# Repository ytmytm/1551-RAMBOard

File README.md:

# 1551-RAMBOard (First Bank)

This project adds **8K of RAM** and **8K of extra ROM space** to a **Commodore 1551** disk drive by replacing the ROM with a small daughterboard. The extra memory is used by a ROM patch to implement a simple **track cache**: read an entire track once, then serve subsequent sector reads from RAM.

A 27x (relative to 1541) / 7x (relative to 1551) fastloader is provided.

The mod and patched ROM are detected and utilized by [Parobek ROM](https://github.com/ytmytm/plus4-parobek).

## What you get

- **RAM expansion**: `$8000-$9FFF` (8K) mapped to SRAM on the daughterboard.
- **Extra ROM window**: `$A000-$BFFF` (8K) mapped to the *upper* part of a larger ROM image.
- **Two DOS ROMs**: with a 64K ROM chip, you can add a switch to select either the stock 1551 ROM or the patched ROM
- **Two patched variants**: stock 1551 (318008-01) and [SuperDOS](https://plus4world.powweb.com/dl/utils/s/super_dos_1551.rom) (40-track disks)
- **HypaRAM**: fastloader
- **Parobek support**: even faster fastloader startup when drivecode is embedded in patched ROM

## Videos

<a href="https://www.youtube.com/watch?v=vWi2URbmIlo" target="_blank">
 <small>Click for 1551 demonstration, loading a 108 block file</small></p>
</a>

<a href="https://www.youtube.com/watch?v=xZMYda7cszA" target="_blank">
 <small>Click for Pi1551 HypaRAM demonstration, loading a 220 block file</small></p>
</a>

## Hardware

This board plugs into the original ROM socket and adds:

- **SRAM**: 8Kx8 (6264) or 32Kx8 (e.g. 62256). Only 8K is used by default; the remaining space is reserved for future banking options.
- **ROM**: 27C512/27E512 (64K). The board maps the active 32K half into `$8000-$FFFF`, but `$8000-$9FFF` is covered by RAM, so effectively the ROM is visible at `$A000-$FFFF` (24K). This is exactly the same setup as DolphinDOS on 1571
- **Glue logic**: `74LS139` + `74LS00`.

### BOM

- 1x 14-pin DIP socket
- 1x 16-pin DIP socket
- 2x 28-pin DIP socket
- 2x 14-pin round pinheaders ("precision" ones)
- 2x 10K resistors
- 1x 74LS00 (or HCT)
- 1x 74LS139 (or HCT)
- 1x 27E256 / 27E512 (32K or 64K EEPROM)
- 1x 6264 or 62256 (8K or 32K SRAM)
- 1x switch (for ROM selection: open or closed)

### Assembly

1. Start by soldering the pin headers to the holes marked "pins". Make sure their longer sections point toward the bottom. The board uses these to plug into the existing ROM socket.

2. Solder the remaining components: two resistors, then the sockets.

3. Flash the EEPROM with a ROM image from the Releases tab (or build your own with `make`). Use `1551.318008-01-64k.bin` for stock DOS or `super_dos_1551-64k.bin` for SuperDOS 40-track support. The 64K image contains the patched ROM in the top half (selected by default when `J1` is open), so you do not need to connect the switch yet.

4. Insert the chips into their sockets.

5. Open the 1551, remove the ROM chip (U4), and plug the board in its place. Ensure correct pin alignment.

6. Connect the remaining signals—`A14`, `A15`, and `R/~W`—as described in the Wiring section below.

### Wiring

- **J1 (ROM bank select for 27C512)**:
  - **short**: bottom 32K of the 64K ROM
  - **open**: top 32K of the 64K ROM
- **J2 (3-wire tap from the 1551 mainboard)**:
  - **A14** from CPU **U2 pin 21** (or **U7 pin 7**)
  - **A15** from CPU **U2 pin 22** (or **U7 pin 6**)
  - **R/~W**: **do not** take raw R/W directly from the CPU. Use the qualified R/~W that actually goes to RAM:
    - onboard RAM **U5 pin 21**, or
    - **U3 pin 19**

### Jumpers

`RAM_A13` and `RAM_A14` jumpers are configured in such a way that you can plug in either SRAM 6264 (8K) or 62256 (32K) with no other changes.
If a method to latch two bits for the necessary port selection is found, then with 62256 (32K) four banks of 8K could be selected - e.g. for a permanent cache of the directory track.

### Quickstart

1. Install the hardware and keep J1 open
2. Use a 27E512 ROM with a 64K image from Releases (`1551.318008-01-64k.bin` or `super_dos_1551-64k.bin`)
3. Try running a simple BASIC program to read the ROM at `$a000` - with J1 open it should be the top, patched half with `RAM` signature
4. If you see `RAM` in the output and you can load the directory then everything works - directory track was already put into cache

```
10 open 15,8,15,"m-r"+chr$(0)+chr$(160)+chr$(3)
20 for i=1 to 3
30 get#15,b$
40 print asc(b$);b$
50 next
60 close 15
```

## Project files (KiCad)

Everything you need is attached to the Release page too.

- [KiCad project](kicad/1551-RAMBoard-FirstBank/)
- [Schematic PDF](kicad/1551-RAMBoard-FirstBank/plots/1551-RAMBoard2-FirstBank.pdf)
- [Gerbers](kicad/1551-RAMBoard-FirstBank/plots/)

## Firmware patch / build

The patcher is a single KickAssembler source file: `rampatch.asm`. It can patch either the stock 1551 ROM or SuperDOS 1551; the Makefile selects the base ROM via KickAssembler `-define` flags (`ROM1551` or `SUPERDOS1551`).

SuperDOS is the only other common 1551 DOS alternative. It adds 40-track disk support (similar in spirit to C64 SpeedDOS/DolphinDOS). The RAMBOard hook sites do not overlap with SuperDOS changes, so the same track-cache patch applies cleanly. Patch4 (ROM checksum bypass) is omitted for the SuperDOS build because SuperDOS already NOPs that routine.

### Source ROMs

Place these in `rom/` (or let `make` download them):

| File | Description |
|------|-------------|
| `rom/1551.318008-01.bin` | Stock 1551 DOS ([zimmers.net](https://www.zimmers.net/anonftp/pub/cbm/firmware/drives/new/1551/1551.318008-01.bin)) |
| `rom/super_dos_1551.bin` | SuperDOS 1551, 40 tracks ([plus4world](https://plus4world.powweb.com/dl/utils/s/super_dos_1551.rom)) |

### Windows (build.bat)

**Requirements**

- Java
- [KickAssembler](http://www.theweb.dk/KickAssembler/Main.html#frontpage) at `tools/KickAss.jar`
- Stock 1551 ROM at `rom/1551.318008-01.bin`

**Build**

```bat
build.bat
```

This builds the stock-ROM variant only:

- `1551.318008-01-patched.bin` — patched 32K ROM image
- `1551.318008-01-64k.bin` — 64K EPROM image (stock ROM in the lower half, patched ROM in the upper half)

For the SuperDOS variant, use the Linux Makefile (or invoke KickAssembler manually with `-define SUPERDOS1551`).

### Linux (Makefile)

**Requirements**

- `make`
- Java
- [KickAssembler](http://www.theweb.dk/KickAssembler/Main.html#frontpage) at `tools/KickAss.jar`
- [ACME](https://sourceforge.net/projects/acme-crossass/) assembler (`acme`)
- `curl` or `wget` (optional; used to auto-download source ROMs)

**Build everything**

```sh
make
```

This produces all deliverables:

| Output | Description |
|--------|-------------|
| `1551.318008-01-patched.bin` | Patched 32K ROM (stock 1551 base) |
| `1551.318008-01-64k.bin` | 64K EPROM image (stock + patched) |
| `super_dos_1551-patched.bin` | Patched 32K ROM (SuperDOS 40-track base) |
| `super_dos_1551-64k.bin` | 64K EPROM image (SuperDOS + patched) |
| `hyparam_1551.prg` | HypaRAM fastloader wedge |

**Other targets**

```sh
make help          # list all targets
make superrom      # SuperDOS patched 32K + 64K images only
make clean         # remove all build outputs (keeps source ROMs in rom/)
make test          # VICE xplus4 with stock patched ROM + RAM expansion
make test-super    # VICE xplus4 with SuperDOS patched ROM + RAM expansion
```

Each 64K image is suitable for 27C512/27E512 EPROMs:

- First 16K: `$FF` bytes (EPROM neutral)
- Next 16K: unpatched base ROM (stock or SuperDOS)
- Upper 32K: patched ROM with track cache and fastloader

## HypaRAM fastloader wedge

An example fastloader wedge called **HypaRAM** is included in the `src/` directory as `hypainstall14f0.s`, which
generates `hyparam_1551.prg`.

When loaded it will intercept LOAD operations and will run the fastloader embedded in the patched drive ROM directly.
With track cache the speedup is approximately **27x** relative to 1541 and **7x** relative to stock 1551.

For simplicity it supports only device #8 and doesn't check if the ROM was patched.

The same fastloader is embedded in [Parobek ROM](https://github.com/ytmytm/plus4-parobek) and will be autodetected for LOAD operations.

### Building HypaRAM

To build the binary `hyparam_1551.prg`, you need the [ACME assembler](https://sourceforge.net/projects/acme-crossass/).

- **Windows**:  
  ```
  acme hypainstall14f0.s
  ```

- **Linux/Unix/WSL**:  
  ```
  make
  ```

The produced binary `hyparam_1551.prg` can be loaded into C16/+4 emulators or real hardware with the RAMBoard installed.

## Testing in VICE

This repo contains `docs/vice-1551-ram-expansion.patch`, which documents the changes needed for VICE to emulate:

- 1551 RAM expansion at `$8000-$9FFF`
- the 32K ROM mapping with RAM overlay

## ROM signature / API stub

The patched ROM contains a small fixed-location signature and a public jump table:

- `$A000-$A002`: ASCII signature `"RAM"` (used to detect that the patched ROM is active)
- `$A003...`: jump table entries

This is used by the HypaRAM fastloader and [Parobek ROM](https://github.com/ytmytm/plus4-parobek).

## Theory of operation

### Address space

The onboard logic enables ROM only in `$C000-$FFFF` range. We ignore this signal and instead use CPU's A15 line as a trigger which signals that `$8000-$FFFF` range is being accessed.

The 74LS139 logic uses A14 to further divide that range to generate chip select signals for RAM in `$8000-$9FFF` range and for ROM in `$A000-$FFFF`.

### Track cache logic

When the drive firmware requests a sector read:

- If the requested track is already cached, the sector is copied from expanded RAM into the target buffer and execution returns to the original ROM flow.
- Otherwise, the patched code reads the entire track, caching **decoded sector data** in expanded RAM and collecting sector numbers from headers to build the lookup table.

The whole track is captured within **one disk revolution** (about **200 ms at 300 rpm**).

### GCR decoding on 1551

Unlike 1541-class drives, the 1551 ROM already decodes GCR **on the fly** during reads (made possible by the 2 MHz CPU). The patch reuses the same approach.

## Related

- design for 1541: [**1541-RAMBOard**](https://github.com/ytmytm/1541-RAMBOardII)
- design for 1571: [**1571 Track Cache ROM**](https://github.com/ytmytm/1571-TrackCacheROM)

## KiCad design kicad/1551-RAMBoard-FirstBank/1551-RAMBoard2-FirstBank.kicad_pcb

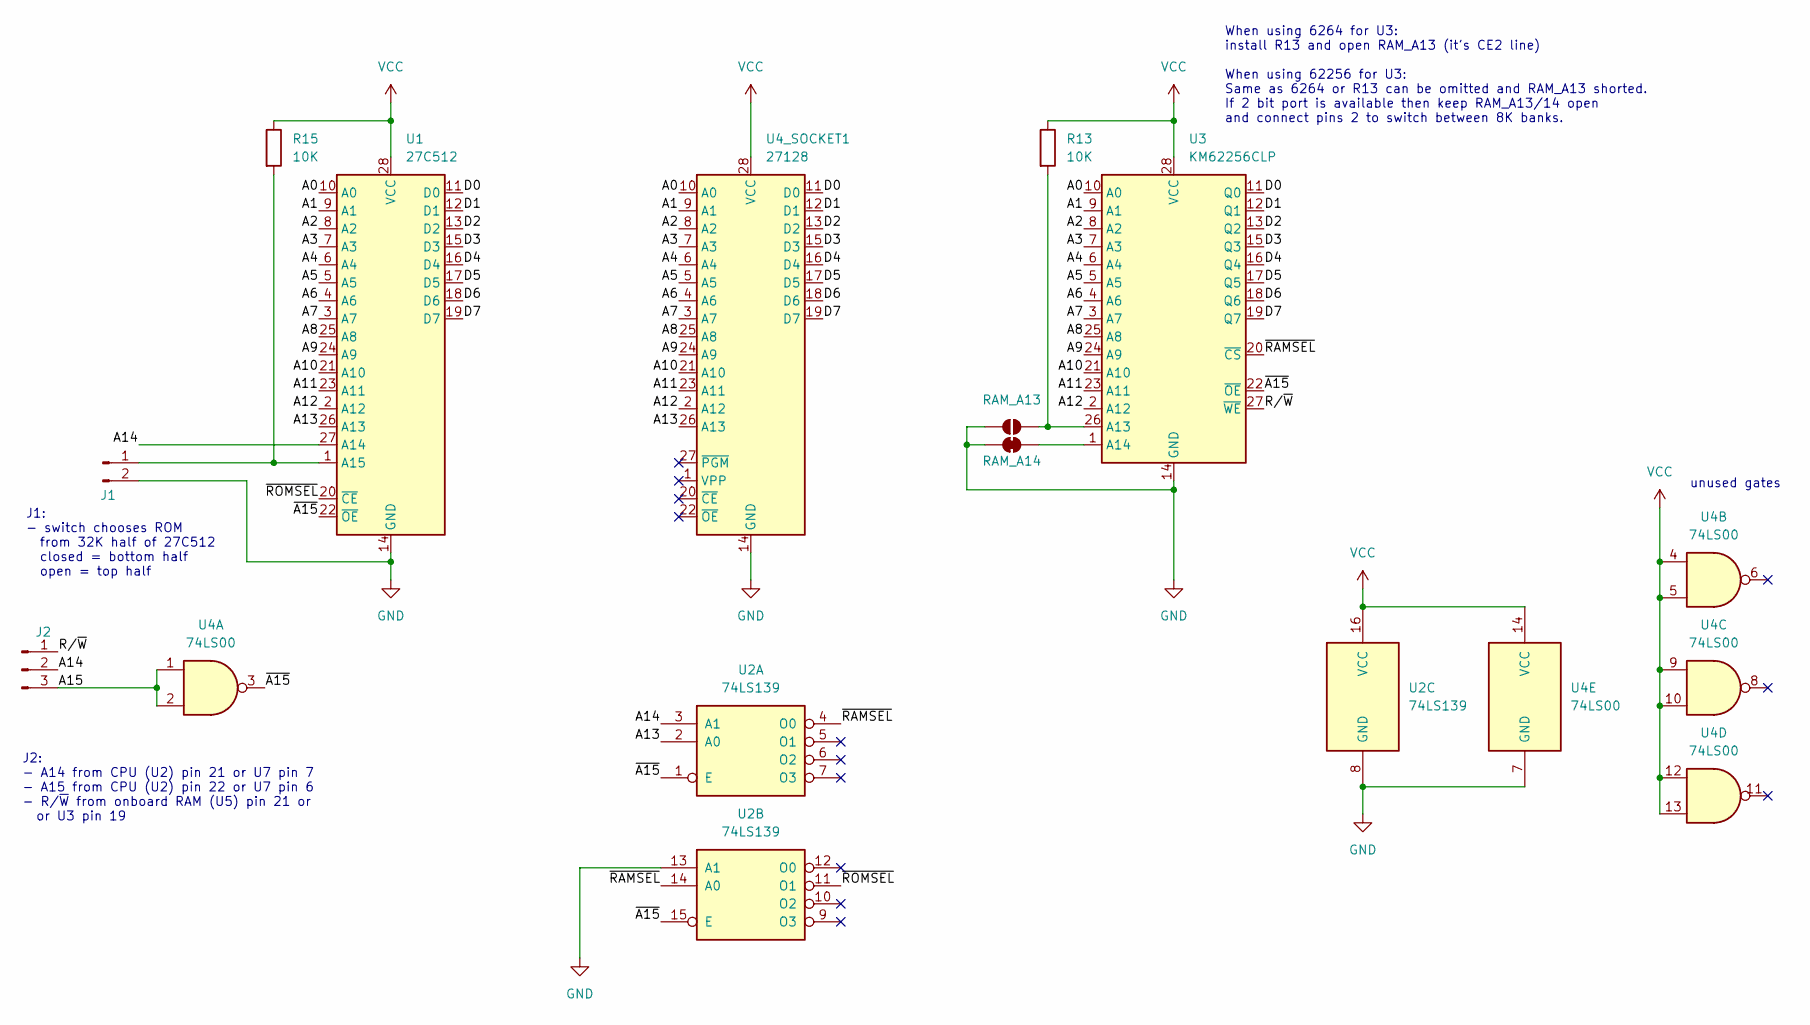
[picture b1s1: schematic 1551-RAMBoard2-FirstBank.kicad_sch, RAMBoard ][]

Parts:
J1: Conn_01x02_Pin; PinHeader_1x02_P2.54mm_Vertical
J2: Conn_01x03_Pin; PinHeader_1x03_P2.54mm_Vertical
R13, R15: 10K; R_Axial_DIN0207_L6.3mm_D2.5mm_P7.62mm_Horizontal
RAM_A13: SolderJumper_2_Open; SolderJumper-2_P1.3mm_Open_RoundedPad1.0x1.5mm
RAM_A14: SolderJumper_2_Bridged; SolderJumper-2_P1.3mm_Bridged_RoundedPad1.0x1.5mm
U1: 27C512; DIP-28_W15.24mm_Socket_LongPads
U2: 74LS139; DIP-16_W7.62mm_Socket_LongPads
U3: KM62256CLP; DIP-28_W15.24mm_Socket_LongPads
U4: 74LS00; DIP-14_W7.62mm_Socket_LongPads
U4_SOCKET1: 27128; DIP-28_W15.24mm_Socket_LongPads

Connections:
/A0: U1.10 (A0), U3.10 (A0), U4_SOCKET1.10 (A0)
/A1: U1.9 (A1), U3.9 (A1), U4_SOCKET1.9 (A1)
/A2: U1.8 (A2), U3.8 (A2), U4_SOCKET1.8 (A2)
/A3: U1.7 (A3), U3.7 (A3), U4_SOCKET1.7 (A3)
/A4: U1.6 (A4), U3.6 (A4), U4_SOCKET1.6 (A4)
/A5: U1.5 (A5), U3.5 (A5), U4_SOCKET1.5 (A5)
/A6: U1.4 (A6), U3.4 (A6), U4_SOCKET1.4 (A6)
/A7: U1.3 (A7), U3.3 (A7), U4_SOCKET1.3 (A7)
/A8: U1.25 (A8), U3.25 (A8), U4_SOCKET1.25 (A8)
/A9: U1.24 (A9), U3.24 (A9), U4_SOCKET1.24 (A9)
/A10: U1.21 (A10), U3.21 (A10), U4_SOCKET1.21 (A10)
/A11: U1.23 (A11), U3.23 (A11), U4_SOCKET1.23 (A11)
/A12: U1.2 (A12), U3.2 (A12), U4_SOCKET1.2 (A12)
/A13: U1.26 (A13), U2.2 (A0), U4_SOCKET1.26 (A13)
/A14: J2.2, U1.27 (A14), U2.3 (A1)
/A15: J2.3, U4.1, U4.2
/D0: U1.11 (D0), U3.11 (Q0), U4_SOCKET1.11 (D0)
/D1: U1.12 (D1), U3.12 (Q1), U4_SOCKET1.12 (D1)
/D2: U1.13 (D2), U3.13 (Q2), U4_SOCKET1.13 (D2)
/D3: U1.15 (D3), U3.15 (Q3), U4_SOCKET1.15 (D3)
/D4: U1.16 (D4), U3.16 (Q4), U4_SOCKET1.16 (D4)
/D5: U1.17 (D5), U3.17 (Q5), U4_SOCKET1.17 (D5)
/D6: U1.18 (D6), U3.18 (Q6), U4_SOCKET1.18 (D6)
/D7: U1.19 (D7), U3.19 (Q7), U4_SOCKET1.19 (D7)
/R/~W: J2.1, U3.27 (~WE)
/~A15: U1.22 (~OE), U2.1 (E), U2.15 (E), U3.22 (~OE), U4.3
/~RAMSEL: U2.4 (O0), U2.14 (A0), U3.20 (~CS)
/~ROMSEL: U1.20 (~CE), U2.11 (O1)
GND: J1.2, RAM_A13.1 (A), RAM_A14.1 (A), U1.14 (GND), U2.8 (GND), U2.13 (A1), U3.14 (GND), U4.7 (GND), U4_SOCKET1.14 (GND)
unnamed: J1.1, R15.2, U1.1 (A15)
unnamed: R13.2, RAM_A13.2 (B), U3.26 (A13)
unnamed: RAM_A14.2 (B), U3.1 (A14)
VCC: R13.1, R15.1, U1.28 (VCC), U2.16 (VCC), U3.28 (VCC), U4.4, U4.5, U4.9, U4.10, U4.12, U4.13, U4.14 (VCC), U4_SOCKET1.28 (VCC)

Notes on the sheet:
When using 6264 for U3: install R13 and open RAM_A13 (it's CE2 line) When using 62256 for U3: Same as 6264 or R13 can be omitted and RAM_A13 shorted. If 2 bit port is available then keep RAM_A13/14 open and connect pins 2 to switch between 8K banks.
J2: - A14 from CPU (U2) pin 21 or U7 pin 7 - A15 from CPU (U2) pin 22 or U7 pin 6 - R/~{W} from onboard RAM (U5) pin 21 or or U3 pin 19
J1: - switch chooses ROM from 32K half of 27C512 closed = bottom half open = top half
unused gates

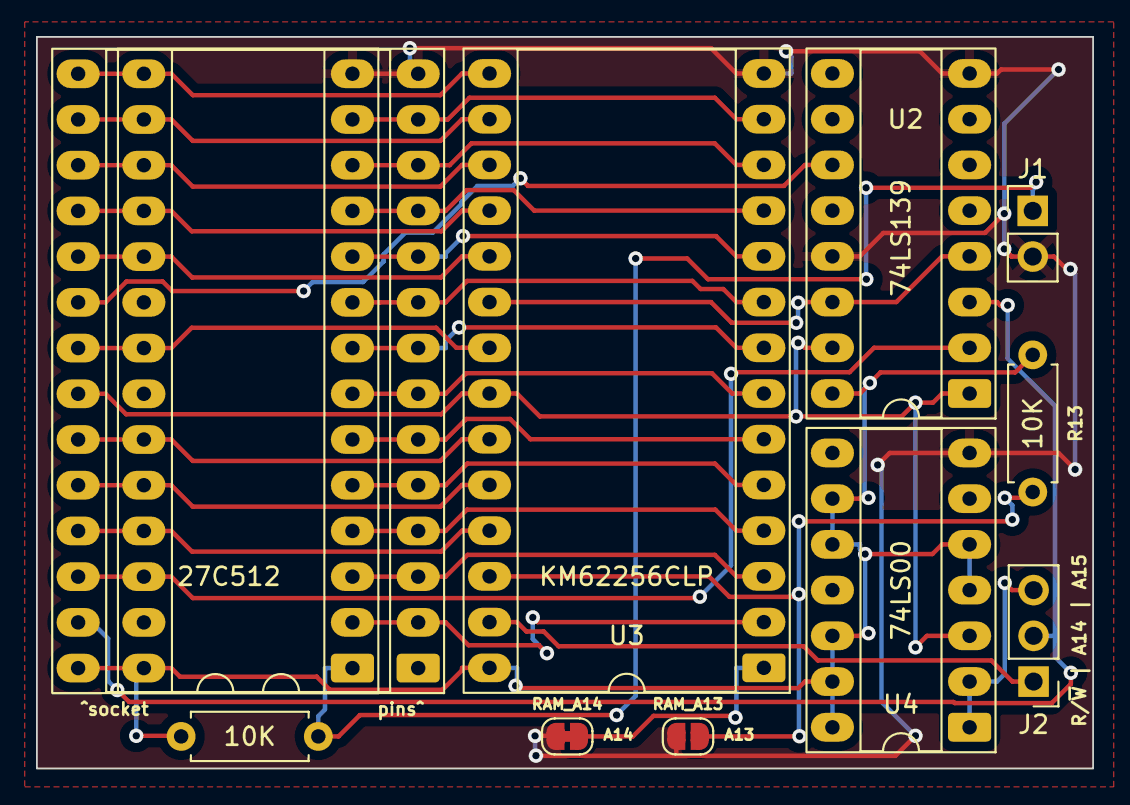
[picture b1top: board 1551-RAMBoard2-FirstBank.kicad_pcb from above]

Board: 2 copper layers, 58.7 x 40.6 mm, 11 parts (0 on the bottom side), 33 nets.

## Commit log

2025-12-21 moving to 1551
2025-12-21 1551 rom disassembly for reference
2025-12-21 1551 photos and schematics
2025-12-21 first attempt
2025-12-21 first try
2025-12-27 remove KiCad backup files
2025-12-27 ignore KiCad backup files
2025-12-27 final touches, support for 6264 (8K) and 62256 (32K)
2025-12-27 remove 1541 ROMs
2025-12-27 more 1551 docs, LLM-augumented for 1541 cross check
2025-12-27 1551 track cache patches, no need for GCR decoding tables, this is already contained in 1551 ROM
2025-12-27 1551 RAMBOard visualization
2025-12-27 story update
2025-12-27 VICE patch to add 1551 RAM expansion at $8000-$9FFF and support 32K ROMs (with RAM overlay)
2025-12-27 docs updated for 1551
2025-12-27 Github actions update
2026-01-11 hypaload 4.7-based embedded loader
2026-01-11 Update Makefile to check for xa binary location before setting XA_PATH in xplus4 and related targets
2026-01-11 fastloader based on HypaLoad 4.7 but with two way handshake
2026-01-11 1551-RAMBOard embedded fastloader completed
2026-01-11 PCB image
2026-01-11 more 1551 photos
2026-01-12 Optimize fastloader by implementing zero-copy data transfer from cache,
2026-01-12 correct ROM load address
2026-01-12 Always transfer load address, handle it on the receiver side
2026-01-17 moved hyparam into src folder
2026-01-17 HypaRAM and 64K ROM image
2026-01-17 update docs
    Updated README to include additional details about the 1551-RAMBOard project, including hardware specifications, quickstart guide, and firmware build instructions.
2026-02-01 updates after real hardware test, clarify R/W connection info
2026-02-01 Revise README for 1551-RAMBOard project
    Updated project description and added images for the 1551-RAMBOard.
2026-02-01 typo
2026-02-01 schematic with drawing sheet
2026-06-15 move bufpage pointer to 0x16 from 0x18 to preserve disk id in header buffer; fix #2
2026-06-16 patches also support SuperDOS-1551 ROM; implemented #3
2026-06-16 SuperDOS makes use of formerly unused 0x16/17 cells, so revert bufpage to 0x18/19 but restore disk ID from 0x14/15
2026-06-16 update CI
2026-06-16 use sector counts from table patched by SuperDOS
